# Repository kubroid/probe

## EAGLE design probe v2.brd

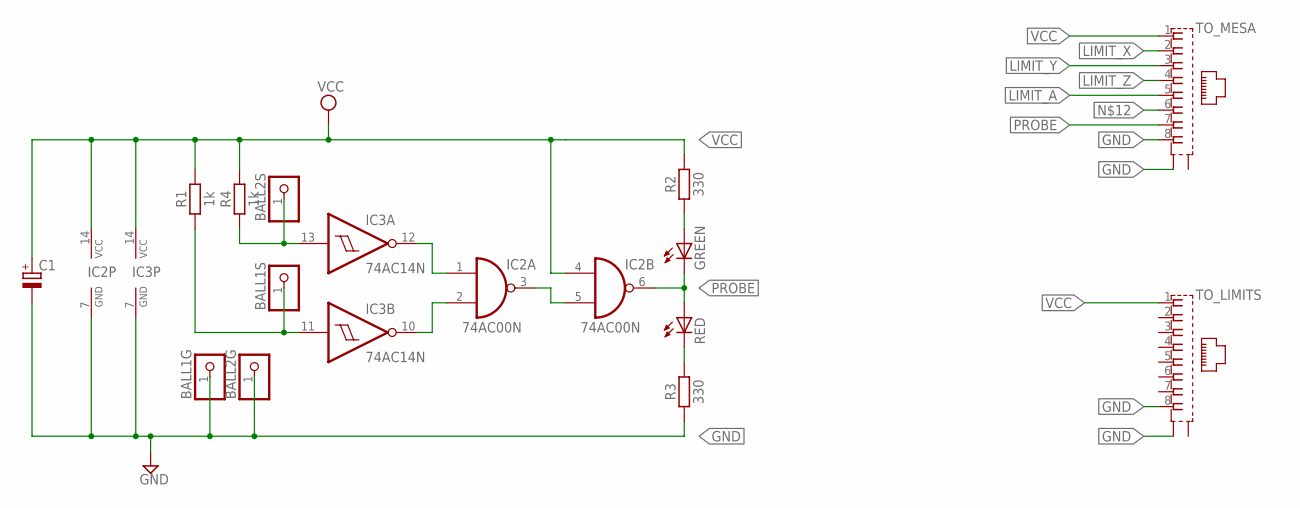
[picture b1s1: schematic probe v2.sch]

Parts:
BALL1G, BALL1S, BALL2G, BALL2S: PINHD-1X1; 1X01
C1: CPOL-EUE5-10.5; E5-10,5
GREEN: LED5MM
IC2: 74AC00N; DIL14
IC3: 74AC14N; DIL14
R1, R4: 1k; 0207/10
R2, R3: 330; 0207/10
RED: LED5MM
TO_LIMITS: 558310-1
TO_MESA: 558310-1

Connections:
BALL: BALL1S.1, IC3.11 (I), R1.1
GND: BALL1G.1, BALL2G.1, C1.-, IC2.7 (GND), IC3.7 (GND), R3.1, TO_LIMITS.8, TO_LIMITS.G2 (S1), TO_MESA.8, TO_MESA.G2 (S1)
LIMIT_A: TO_MESA.5
LIMIT_X: TO_MESA.2
LIMIT_Y: TO_MESA.3
LIMIT_Z: TO_MESA.4
unnamed: GREEN.A, R2.1
unnamed: R3.2, RED.K (C)
unnamed: IC2.1 (I0), IC3.12 (O)
unnamed: IC2.2 (I1), IC3.10 (O)
unnamed: BALL2S.1, IC3.13 (I), R4.1
unnamed: IC2.3 (O), IC2.5 (I1)
PROBE: GREEN.K (C), IC2.6 (O), RED.A, TO_MESA.7
VCC: C1.+, IC2.4 (I0), IC2.14 (VCC), IC3.14 (VCC), R1.2, R2.2, R4.2, TO_LIMITS.1, TO_MESA.1

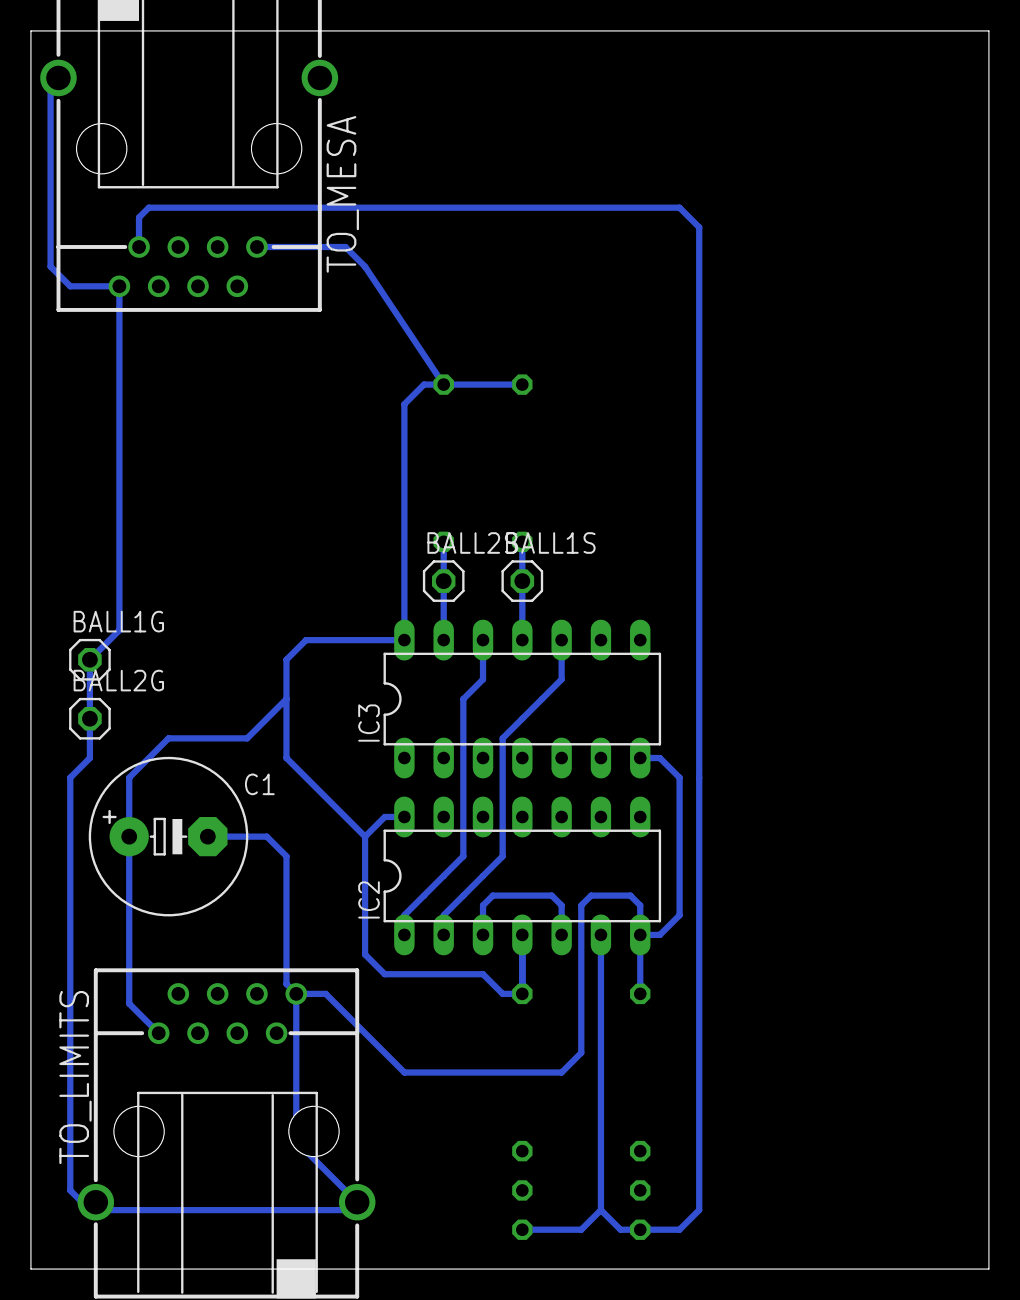
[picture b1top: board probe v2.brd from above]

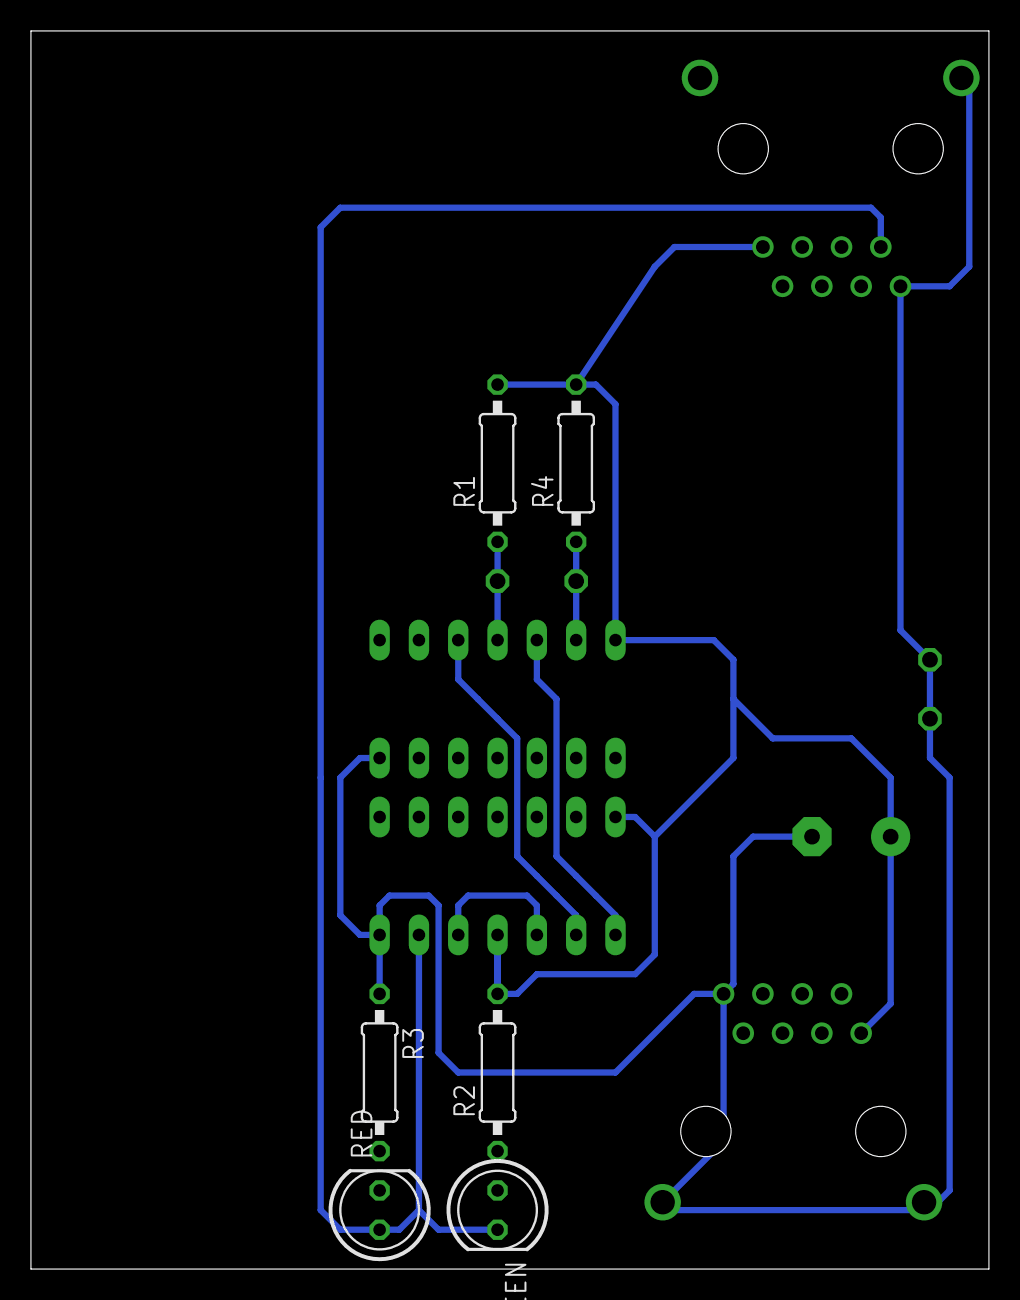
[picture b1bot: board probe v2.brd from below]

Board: 2 copper layers, 61.9 x 80.0 mm, 15 parts (6 on the bottom side), 10 nets.

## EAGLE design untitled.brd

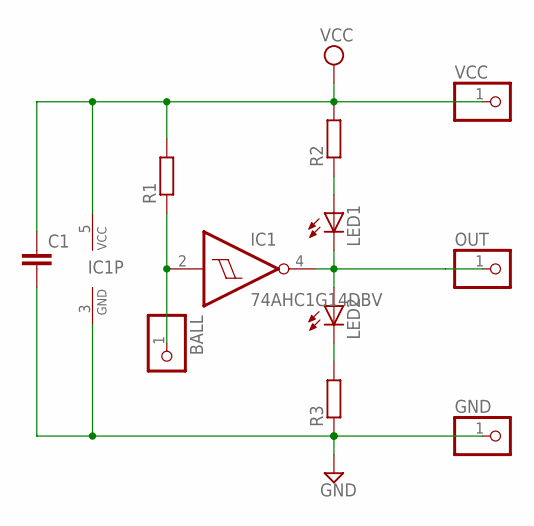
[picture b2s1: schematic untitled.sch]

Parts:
BALL: PINHD-1X1; 1X01
C1: C-EUC0805; C0805
GND: PINHD-1X1; 1X01
IC1: 74AHC1G14DBV; SOT23-5
LED1, LED2: LEDCHIP-LED0805; CHIP-LED0805
OUT: PINHD-1X1; 1X01
R1, R2, R3: R-EU_R0805; R0805
VCC: PINHD-1X1; 1X01

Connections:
BALL: BALL.1, IC1.2 (I), R1.1
GND: C1.2, GND.1, IC1.3 (GND), R3.1
unnamed: LED1.A, R2.1
unnamed: LED2.C, R3.2
OUT: IC1.4 (O), LED1.C, LED2.A, OUT.1
VCC: C1.1, IC1.5 (VCC), R1.2, R2.2, VCC.1

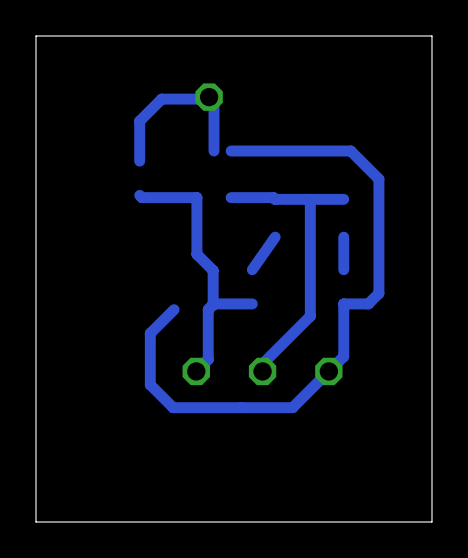
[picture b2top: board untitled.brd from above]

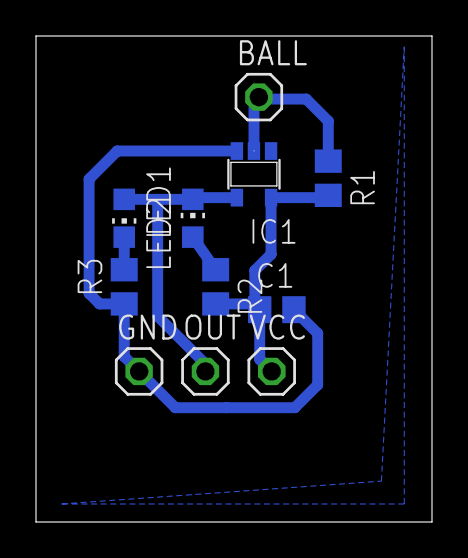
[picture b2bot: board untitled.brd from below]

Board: 2 copper layers, 22.0 x 27.0 mm, 11 parts (11 on the bottom side), 6 nets.

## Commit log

2013-11-04 First try to make a connection box directly on machine
2013-11-05 Compacted
